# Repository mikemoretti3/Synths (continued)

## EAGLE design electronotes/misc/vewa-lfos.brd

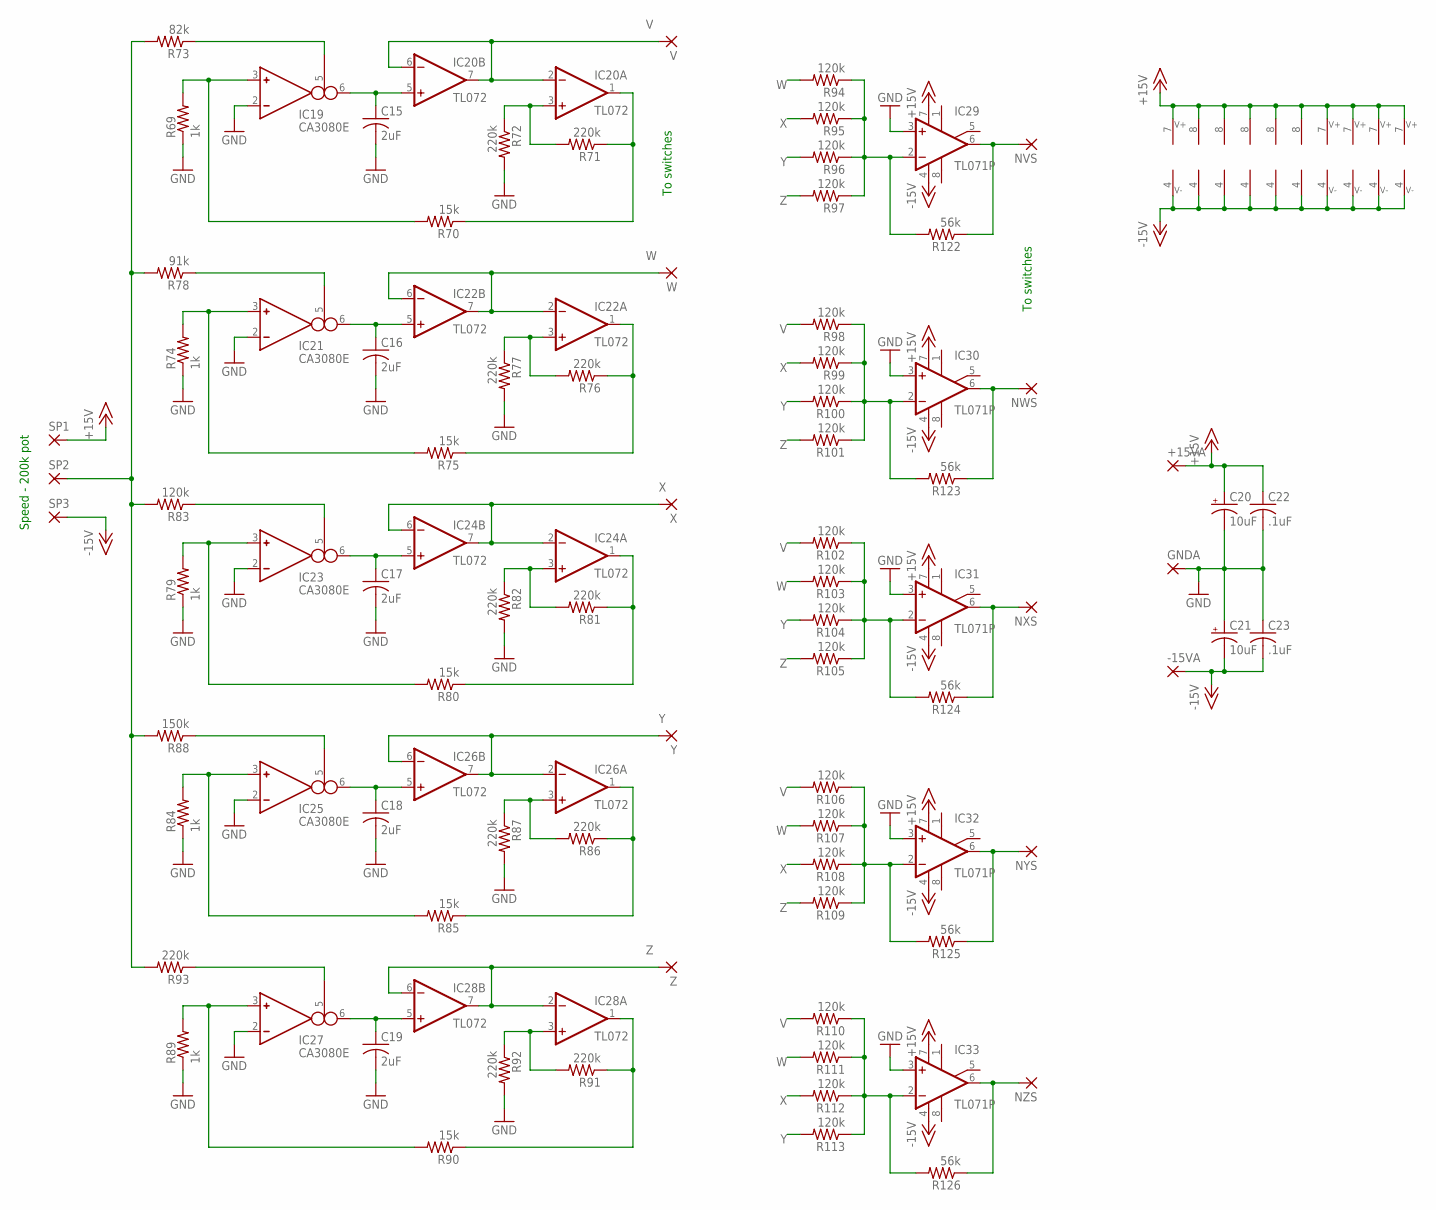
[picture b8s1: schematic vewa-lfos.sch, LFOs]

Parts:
+15VA: 2,54/1,0
-15VA: 2,54/1,0
C15, C16, C17, C18, C19: 2uF; C050-025X075
C20, C21: 10uF; E2,5-5
C22, C23: .1uF; C050-025X075
GNDA: 2,54/1,0
IC19, IC21, IC23, IC25, IC27: CA3080E; DIL08
IC20, IC22, IC24, IC26, IC28: TL072; DIL08
IC29, IC30, IC31, IC32, IC33: TL071P; DIL08
NVS: 2,54/1,0
NWS: 2,54/1,0
NXS: 2,54/1,0
NYS: 2,54/1,0
NZS: 2,54/1,0
R69, R74, R79, R84, R89: 1k; 0207/10
R70, R75, R80, R85, R90: 15k; 0207/10
R71, R72, R76, R77, R81, R82, R86, R87, R91, R92, R93: 220k; 0207/10
R73: 82k; 0207/10
R78: 91k; 0207/10
R83, R94, R95, R96, R97, R98, R99, R100, R101, R102, R103, R104, R105, R106, R107, R108, R109, R110, R111, R112, R113: 120k; 0207/10
R88: 150k; 0207/10
R122, R123, R124, R125, R126: 56k; 0207/10
SP1, SP2, SP3: 2,54/1,0
V: 2,54/1,0
W: 2,54/1,0
X: 2,54/1,0
Y: 2,54/1,0
Z: 2,54/1,0

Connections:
+15V: +15VA.1, C20.+, C22.1, IC19.7, IC20.8 (V+), IC21.7, IC22.8 (V+), IC23.7, IC24.8 (V+), IC25.7, IC26.8 (V+), IC27.7, IC28.8 (V+), IC29.7 (V+), IC30.7 (V+), IC31.7 (V+), IC32.7 (V+), IC33.7 (V+), SP1.1
-15V: -15VA.1, C21.-, C23.2, IC19.4, IC20.4 (V-), IC21.4, IC22.4 (V-), IC23.4, IC24.4 (V-), IC25.4, IC26.4 (V-), IC27.4, IC28.4 (V-), IC29.4 (V-), IC30.4 (V-), IC31.4 (V-), IC32.4 (V-), IC33.4 (V-), SP3.1
GND: C15.2, C16.2, C17.2, C18.2, C19.2, C20.-, C21.+, C22.2, C23.1, GNDA.1, IC19.2 (IN_N), IC21.2 (IN_N), IC23.2 (IN_N), IC25.2 (IN_N), IC27.2 (IN_N), IC29.3 (+IN), IC30.3 (+IN), IC31.3 (+IN), IC32.3 (+IN), IC33.3 (+IN), R69.1, R72.2, R74.1, R77.2, R79.1, R82.2, R84.1, R87.2, R89.1, R92.2
unnamed: C15.1, IC19.6 (OUT), IC20.5 (+IN)
unnamed: IC20.3 (+IN), R71.2, R72.1
unnamed: IC20.1 (OUT), R70.1, R71.1
unnamed: IC19.3 (IN_P), R69.2, R70.2
unnamed: IC19.5 (I_BIAS), R73.1
unnamed: C16.1, IC21.6 (OUT), IC22.5 (+IN)
unnamed: IC22.3 (+IN), R76.2, R77.1
unnamed: IC22.1 (OUT), R75.1, R76.1
unnamed: IC21.3 (IN_P), R74.2, R75.2
unnamed: IC21.5 (I_BIAS), R78.1
unnamed: IC29.2 (-IN), R94.1, R95.1, R96.1, R97.1, R122.2
unnamed: C17.1, IC23.6 (OUT), IC24.5 (+IN)
unnamed: IC24.3 (+IN), R81.2, R82.1
unnamed: IC24.1 (OUT), R80.1, R81.1
unnamed: IC23.3 (IN_P), R79.2, R80.2
unnamed: IC23.5 (I_BIAS), R83.1
unnamed: IC30.2 (-IN), R98.1, R99.1, R100.1, R101.1, R123.2
unnamed: IC31.2 (-IN), R102.1, R103.1, R104.1, R105.1, R124.2
unnamed: C18.1, IC25.6 (OUT), IC26.5 (+IN)
unnamed: IC26.3 (+IN), R86.2, R87.1
unnamed: IC26.1 (OUT), R85.1, R86.1
unnamed: IC25.3 (IN_P), R84.2, R85.2
unnamed: IC25.5 (I_BIAS), R88.1
unnamed: IC32.2 (-IN), R106.1, R107.1, R108.1, R109.1, R125.2
unnamed: IC33.2 (-IN), R110.1, R111.1, R112.1, R113.1, R126.2
unnamed: C19.1, IC27.6 (OUT), IC28.5 (+IN)
unnamed: IC28.3 (+IN), R91.2, R92.1
unnamed: IC28.1 (OUT), R90.1, R91.1
unnamed: IC27.3 (IN_P), R89.2, R90.2
unnamed: IC27.5 (I_BIAS), R93.1
unnamed: R73.2, R78.2, R83.2, R88.2, R93.2, SP2.1
NVS: IC29.6 (OUT), NVS.1, R122.1
NWS: IC30.6 (OUT), NWS.1, R123.1
NXS: IC31.6 (OUT), NXS.1, R124.1
NYS: IC32.6 (OUT), NYS.1, R125.1
NZS: IC33.6 (OUT), NZS.1, R126.1
V: IC20.2 (-IN), IC20.6 (-IN), IC20.7 (OUT), R98.2, R102.2, R106.2, R110.2, V.1
W: IC22.2 (-IN), IC22.6 (-IN), IC22.7 (OUT), R94.2, R103.2, R107.2, R111.2, W.1
X: IC24.2 (-IN), IC24.6 (-IN), IC24.7 (OUT), R95.2, R99.2, R108.2, R112.2, X.1
Y: IC26.2 (-IN), IC26.6 (-IN), IC26.7 (OUT), R96.2, R100.2, R104.2, R113.2, Y.1
Z: IC28.2 (-IN), IC28.6 (-IN), IC28.7 (OUT), R97.2, R101.2, R105.2, R109.2, Z.1

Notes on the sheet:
Speed - 200k pot
To switches

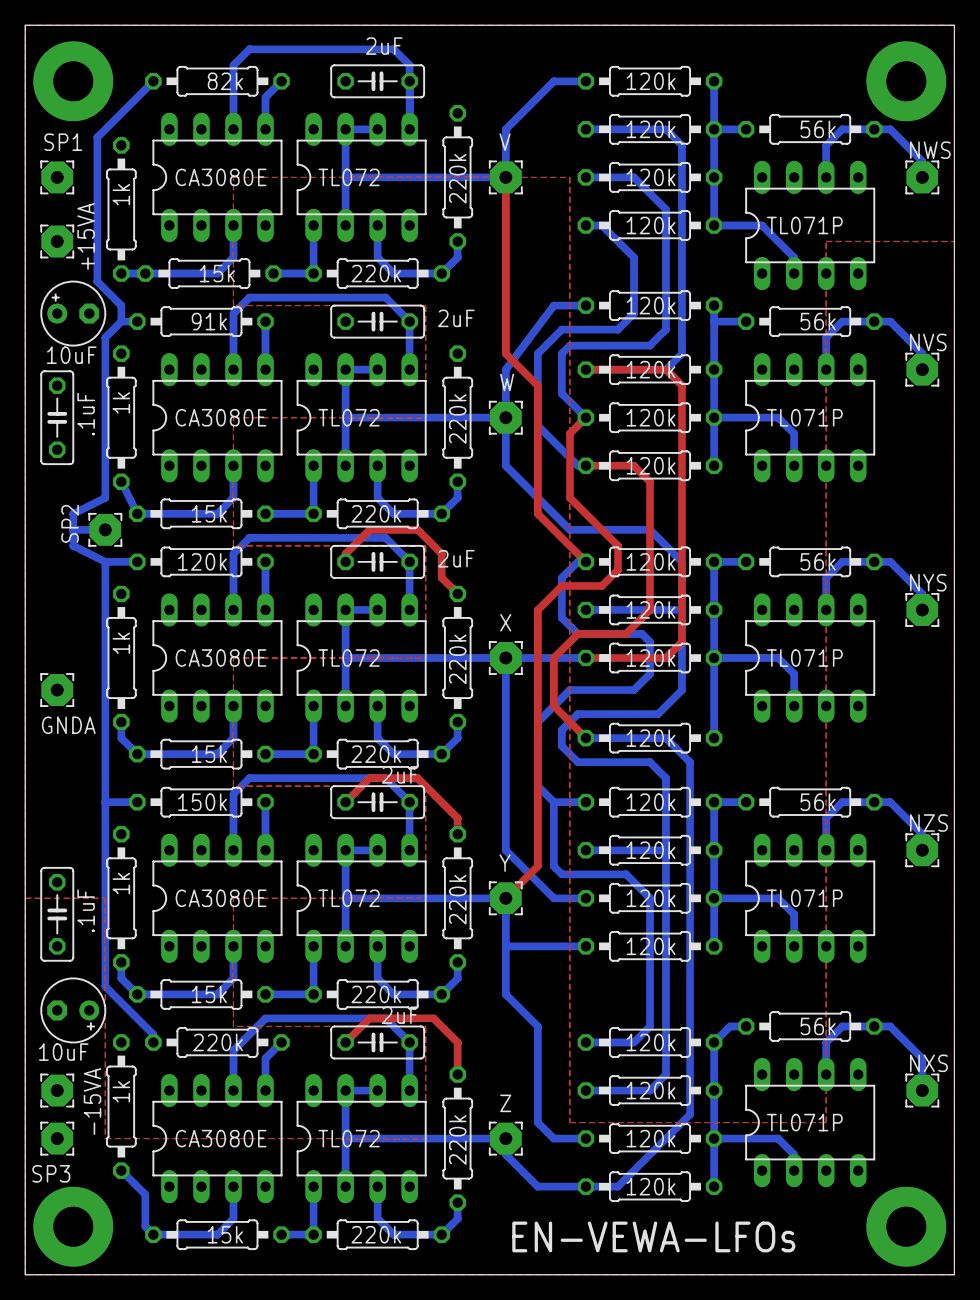
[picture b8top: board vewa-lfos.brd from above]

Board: 2 copper layers, 73.7 x 99.1 mm, 90 parts (0 on the bottom side), 44 nets.
